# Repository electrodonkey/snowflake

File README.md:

# snowflake

RF controlled Christmas decoration

## architecture

- MCU: TI MSPM0L1306
- LED DRIVER: TI LP5569
- SUB-GHz: ST S2-LP
- POWER: CR2032

## hardware

[schematic pdf](hardware/output/snowflake.pdf)

## licence

Copyright 2023 Dan Chirciu (electrodonkey)

Permission is hereby granted, free of charge, to any person obtaining a copy of this software and associated documentation files (the “Software”), to deal in the Software without restriction, including without limitation the rights to use, copy, modify, merge, publish, distribute, sublicense, and/or sell copies of the Software, and to permit persons to whom the Software is furnished to do so, subject to the following conditions:

The above copyright notice and this permission notice shall be included in all copies or substantial portions of the Software.

THE SOFTWARE IS PROVIDED “AS IS”, WITHOUT WARRANTY OF ANY KIND, EXPRESS OR IMPLIED, INCLUDING BUT NOT LIMITED TO THE WARRANTIES OF MERCHANTABILITY, FITNESS FOR A PARTICULAR PURPOSE AND NONINFRINGEMENT. IN NO EVENT SHALL THE AUTHORS OR COPYRIGHT HOLDERS BE LIABLE FOR ANY CLAIM, DAMAGES OR OTHER LIABILITY, WHETHER IN AN ACTION OF CONTRACT, TORT OR OTHERWISE, ARISING FROM, OUT OF OR IN CONNECTION WITH THE SOFTWARE OR THE USE OR OTHER DEALINGS IN THE SOFTWARE.

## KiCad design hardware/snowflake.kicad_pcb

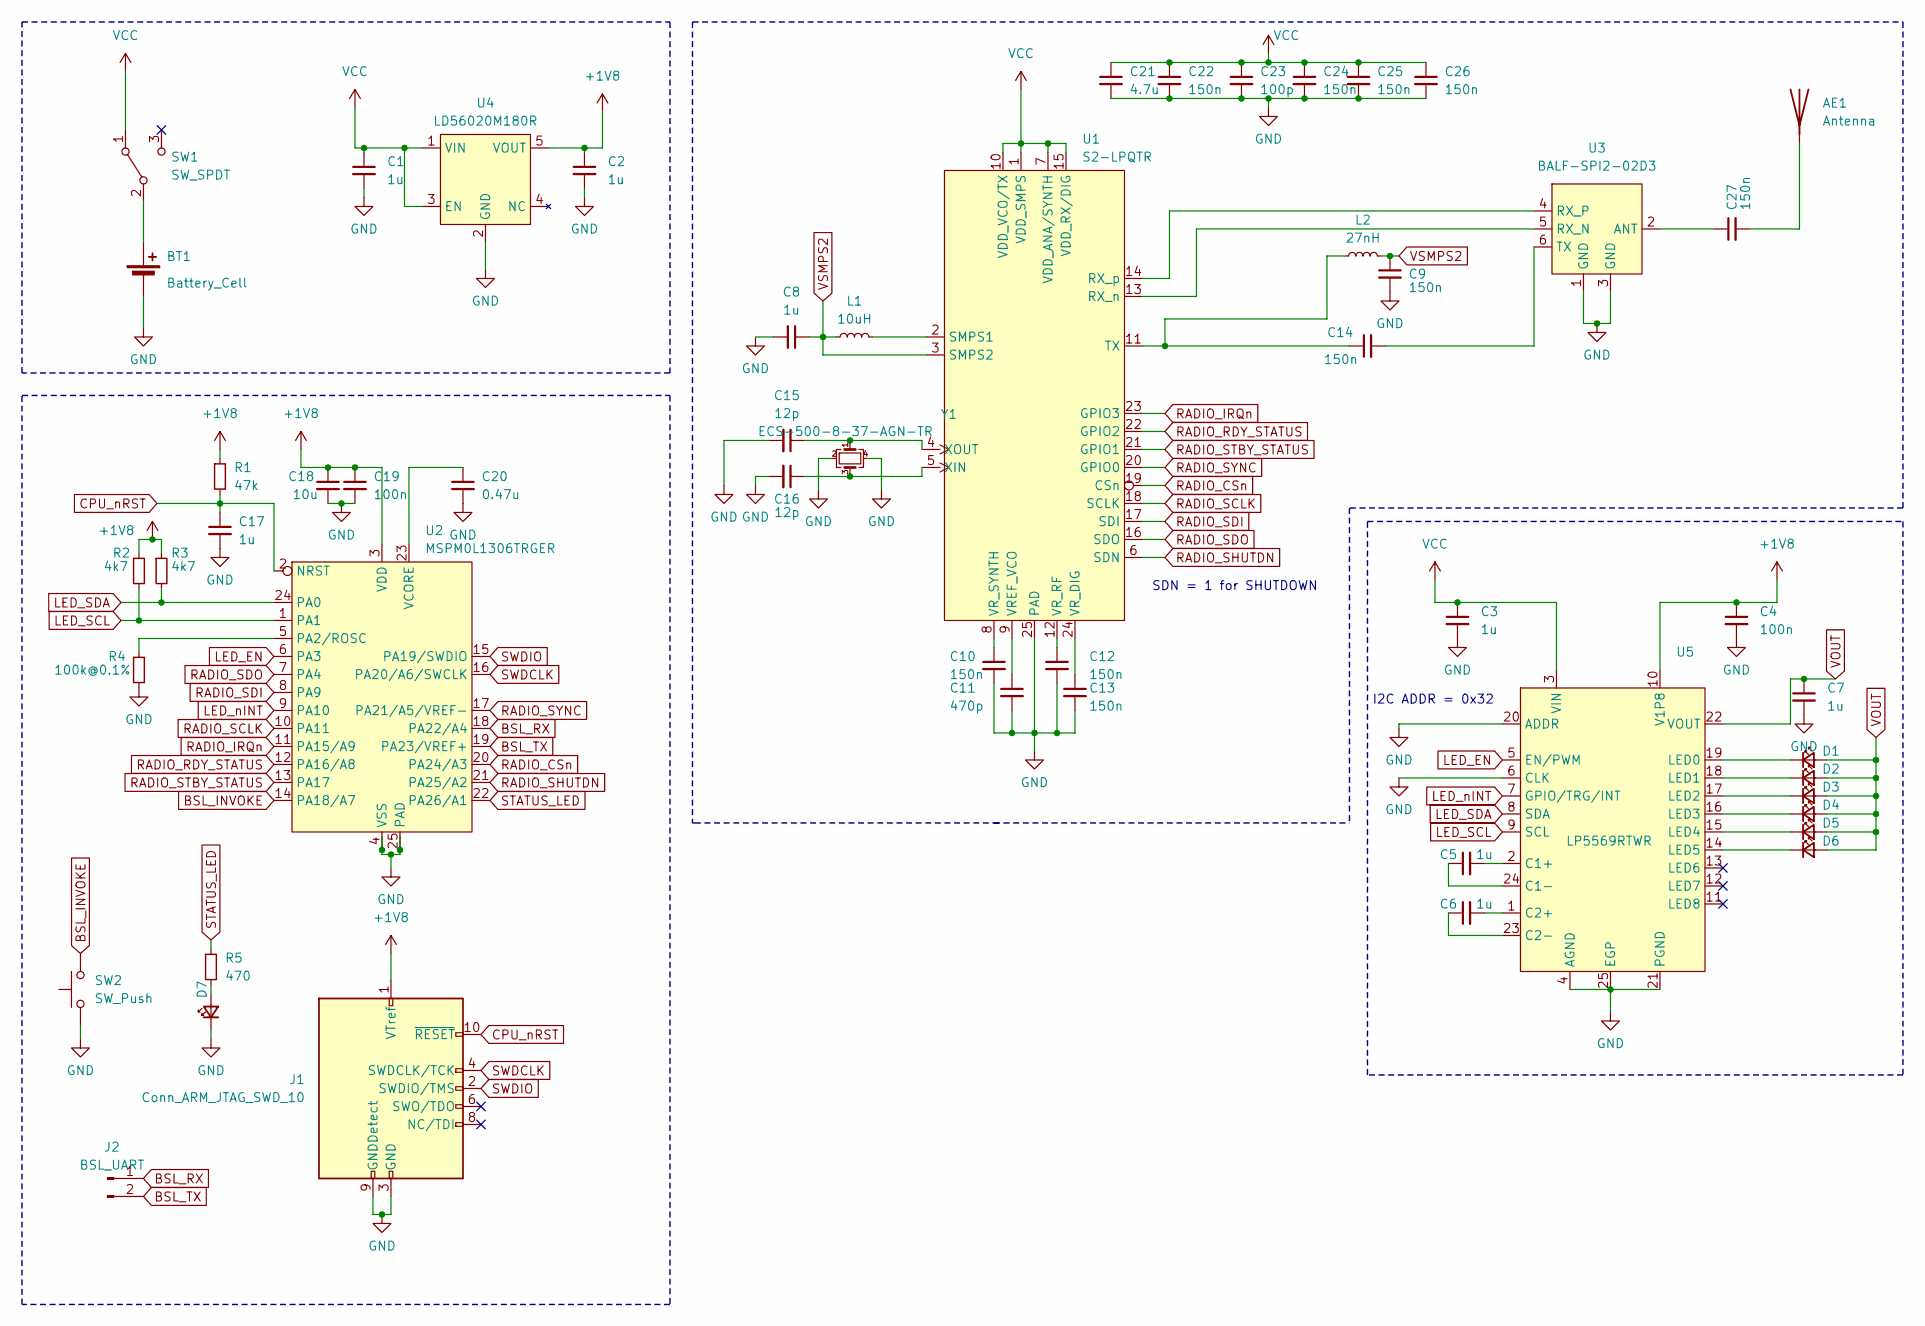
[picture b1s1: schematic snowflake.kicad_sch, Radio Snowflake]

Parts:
AE1: Antenna; ANT-418-HETH
BT1: Battery_Cell; BatteryHolder_Keystone_3034_1x20mm
C1, C2, C3, C5, C6, C7, C8, C17: 1u; C_0603_1608Metric_Pad1.08x0.95mm_HandSolder
C4, C19: 100n; C_0603_1608Metric_Pad1.08x0.95mm_HandSolder
C9, C10, C12, C13, C14, C22, C24, C25, C26, C27: 150n; C_0603_1608Metric_Pad1.08x0.95mm_HandSolder
C11: 470p; C_0603_1608Metric_Pad1.08x0.95mm_HandSolder
C15, C16: 12p; C_0603_1608Metric_Pad1.08x0.95mm_HandSolder
C18: 10u; C_0603_1608Metric_Pad1.08x0.95mm_HandSolder
C20: 0.47u; C_0603_1608Metric_Pad1.08x0.95mm_HandSolder
C21: 4.7u; C_0603_1608Metric_Pad1.08x0.95mm_HandSolder
C23: 100p; C_0603_1608Metric_Pad1.08x0.95mm_HandSolder
D1, D2, D3, D4, D5, D6, D7: LED; LED_1206_3216Metric_Pad1.42x1.75mm_HandSolder
J1: Conn_ARM_JTAG_SWD_10; PinHeader_2x05_P1.27mm_Vertical
J2: BSL_UART; PinHeader_1x02_P1.27mm_Vertical
L1: 10uH; L_0603_1608Metric_Pad1.05x0.95mm_HandSolder
L2: 27nH; L_0603_1608Metric_Pad1.05x0.95mm_HandSolder
R1: 47k; R_0603_1608Metric_Pad0.98x0.95mm_HandSolder
R2, R3: 4k7; R_0603_1608Metric_Pad0.98x0.95mm_HandSolder
R4: 100k@0.1%; R_0603_1608Metric_Pad0.98x0.95mm_HandSolder
R5: 470; R_0603_1608Metric_Pad0.98x0.95mm_HandSolder
SW1: SW_SPDT; SW_SPDT_PCM12
SW2: SW_Push; SW_SPST_Omron_B3FS-100xP
U1: S2-LPQTR; QFN-24-1EP_4x4mm_P0.5mm_EP2.7x2.7mm
U2: MSPM0L1306TRGER; Texas_RGE0024C_EP2.1x2.1mm
U3: BALF-SPI2-02D3; balf-spi2-01d3
U4: LD56020M180R; SOT-23-5_HandSoldering
U5: LP5569RTWR; WQFN-24-1EP_4x4mm_P0.5mm_EP2.6x2.6mm
Y1: ECS-500-8-37-AGN-TR; Crystal_SMD_2016-4Pin_2.0x1.6mm

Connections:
+1V8: C2.1, C4.1, C18.1, C19.1, J1.1 (VTref), R1.1, R2.1, R3.1, U2.3 (VDD), U4.5 (VOUT), U5.10 (V1P8)
BSL_INVOKE: SW2.2, U2.14 (PA18/A7)
BSL_RX: J2.1, U2.18 (PA22/A4)
BSL_TX: J2.2, U2.19 (PA23/VREF+)
CPU_nRST: C17.1, J1.10 (~RESET), R1.2, U2.2 (NRST)
GND: BT1.2 (-), C1.2, C2.2, C3.2, C4.2, C7.2, C8.2, C9.2, C10.2, C11.2, C12.2, C13.2, C15.2, C16.2, C17.2, C18.2, C19.2, C20.2, C21.2, C22.2, C23.2, C24.2, C25.2, C26.2, D7.1 (K), J1.3 (GND), J1.5 (GND), J1.9 (GNDDetect), R4.2, SW2.1, U1.25 (PAD), U2.4 (VSS), U2.25 (PAD), U3.1 (GND), U3.3 (GND), U4.2 (GND), U5.4 (AGND), U5.6 (CLK), U5.20 (ADDR), U5.21 (PGND), U5.25 (EGP), Y1.2, Y1.4
LED_EN: U2.6 (PA3), U5.5 (EN/PWM)
LED_SCL: R2.2, U2.1 (PA1), U5.9 (SCL)
LED_SDA: R3.2, U2.24 (PA0), U5.8 (SDA)
LED_nINT: U2.9 (PA10), U5.7 (GPIO/TRG/INT)
unnamed: AE1.1 (A), C27.2
unnamed: BT1.1 (+), SW1.2 (B)
unnamed: D1.1 (K), U5.19 (LED0)
unnamed: D2.1 (K), U5.18 (LED1)
unnamed: D3.1 (K), U5.17 (LED2)
unnamed: D4.1 (K), U5.16 (LED3)
unnamed: D5.1 (K), U5.15 (LED4)
unnamed: D6.1 (K), U5.14 (LED5)
unnamed: D7.2 (A), R5.2
unnamed: U1.13 (RX_n), U3.5 (RX_N)
unnamed: U1.14 (RX_p), U3.4 (RX_P)
unnamed: L1.2, U1.2 (SMPS1)
unnamed: C14.1, L2.1, U1.11 (TX)
unnamed: C11.1, U1.9 (VREF_VCO)
unnamed: C13.1, U1.24 (VR_DIG)
unnamed: C12.1, U1.12 (VR_RF)
unnamed: C10.1, U1.8 (VR_SYNTH)
unnamed: C16.1, U1.5 (XIN), Y1.3
unnamed: C15.1, U1.4 (XOUT), Y1.1
unnamed: R4.1, U2.5 (PA2/ROSC)
unnamed: C20.1, U2.23 (VCORE)
unnamed: C27.1, U3.2 (ANT)
unnamed: C14.2, U3.6 (TX)
unnamed: C5.2, U5.2 (C1+)
unnamed: C5.1, U5.24 (C1-)
unnamed: C6.2, U5.1 (C2+)
unnamed: C6.1, U5.23 (C2-)
RADIO_CSn: U1.19 (CSn), U2.20 (PA24/A3)
RADIO_IRQn: U1.23 (GPIO3), U2.11 (PA15/A9)
RADIO_RDY_STATUS: U1.22 (GPIO2), U2.12 (PA16/A8)
RADIO_SCLK: U1.18 (SCLK), U2.10 (PA11)
RADIO_SDI: U1.17 (SDI), U2.8 (PA9)
RADIO_SDO: U1.16 (SDO), U2.7 (PA4)
RADIO_SHUTDN: U1.6 (SDN), U2.21 (PA25/A2)
RADIO_STBY_STATUS: U1.21 (GPIO1), U2.13 (PA17)
RADIO_SYNC: U1.20 (GPIO0), U2.17 (PA21/A5/VREF-)
STATUS_LED: R5.1, U2.22 (PA26/A1)
SWDCLK: J1.4 (SWDCLK/TCK), U2.16 (PA20/A6/SWCLK)
SWDIO: J1.2 (SWDIO/TMS), U2.15 (PA19/SWDIO)
VCC: C1.1, C3.1, C21.1, C22.1, C23.1, C24.1, C25.1, C26.1, SW1.1 (A), U1.1 (VDD_SMPS), U1.7 (VDD_ANA/SYNTH), U1.10 (VDD_VCO/TX), U1.15 (VDD_RX/DIG), U4.1 (VIN), U4.3 (EN), U5.3 (VIN)
VOUT: C7.1, D1.2 (A), D2.2 (A), D3.2 (A), D4.2 (A), D5.2 (A), D6.2 (A), U5.22 (VOUT)
VSMPS2: C8.1, C9.1, L1.1, L2.2, U1.3 (SMPS2)

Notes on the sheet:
I2C ADDR = 0x32
SDN = 1 for SHUTDOWN

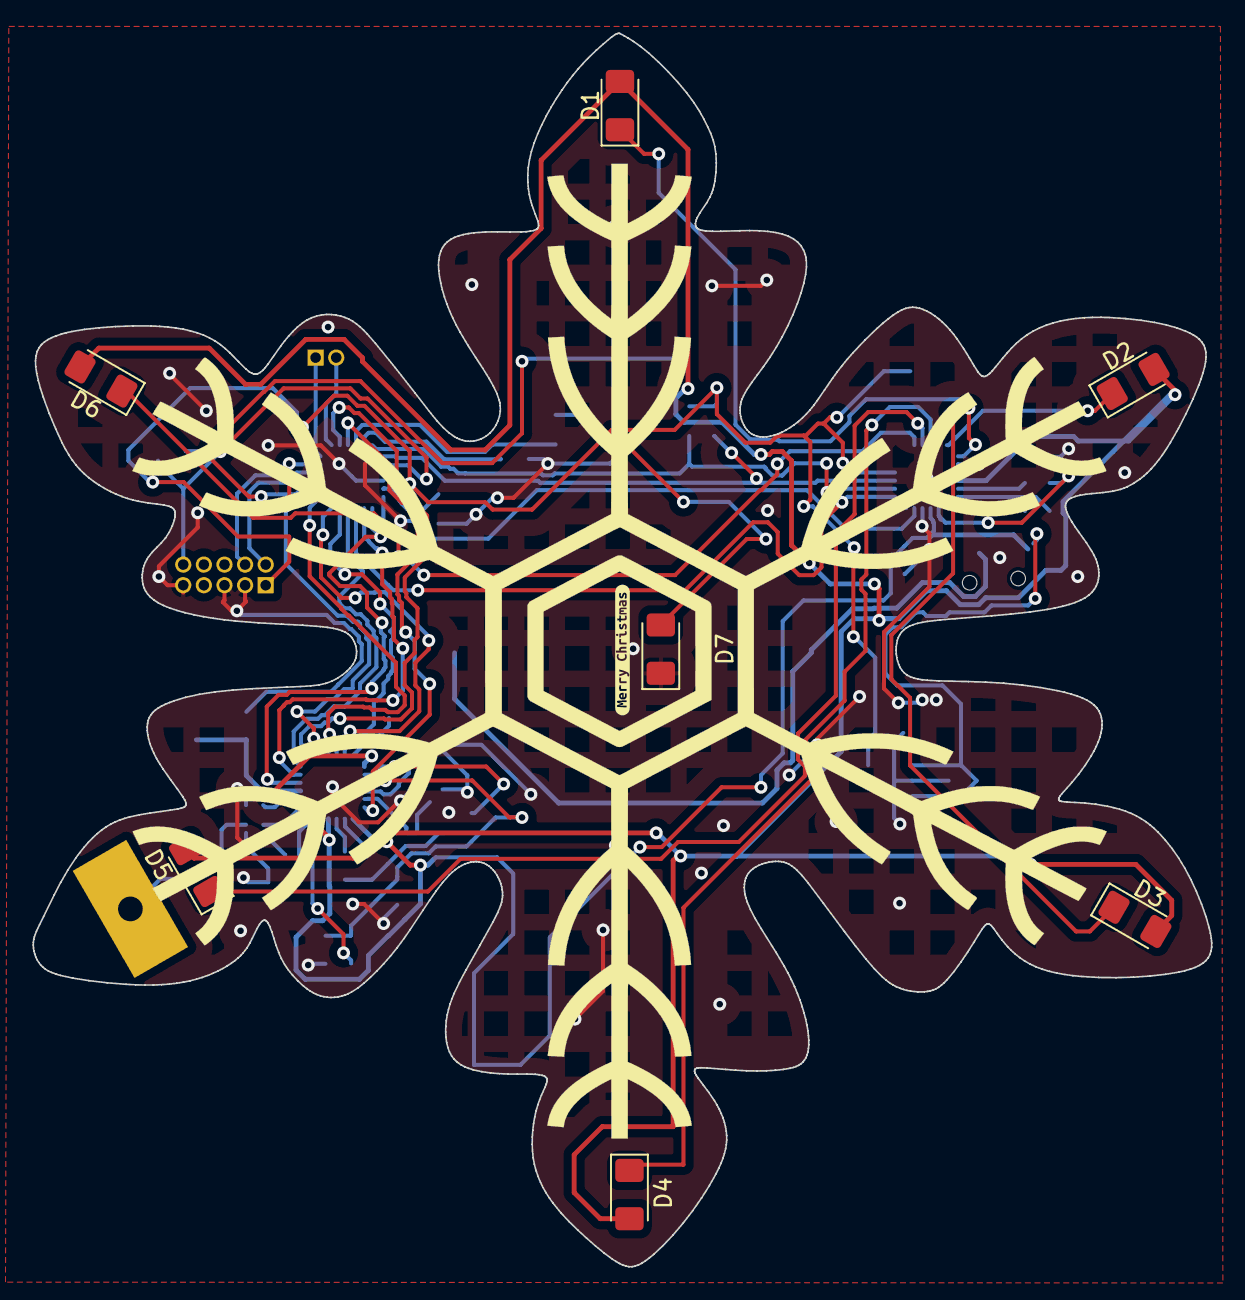
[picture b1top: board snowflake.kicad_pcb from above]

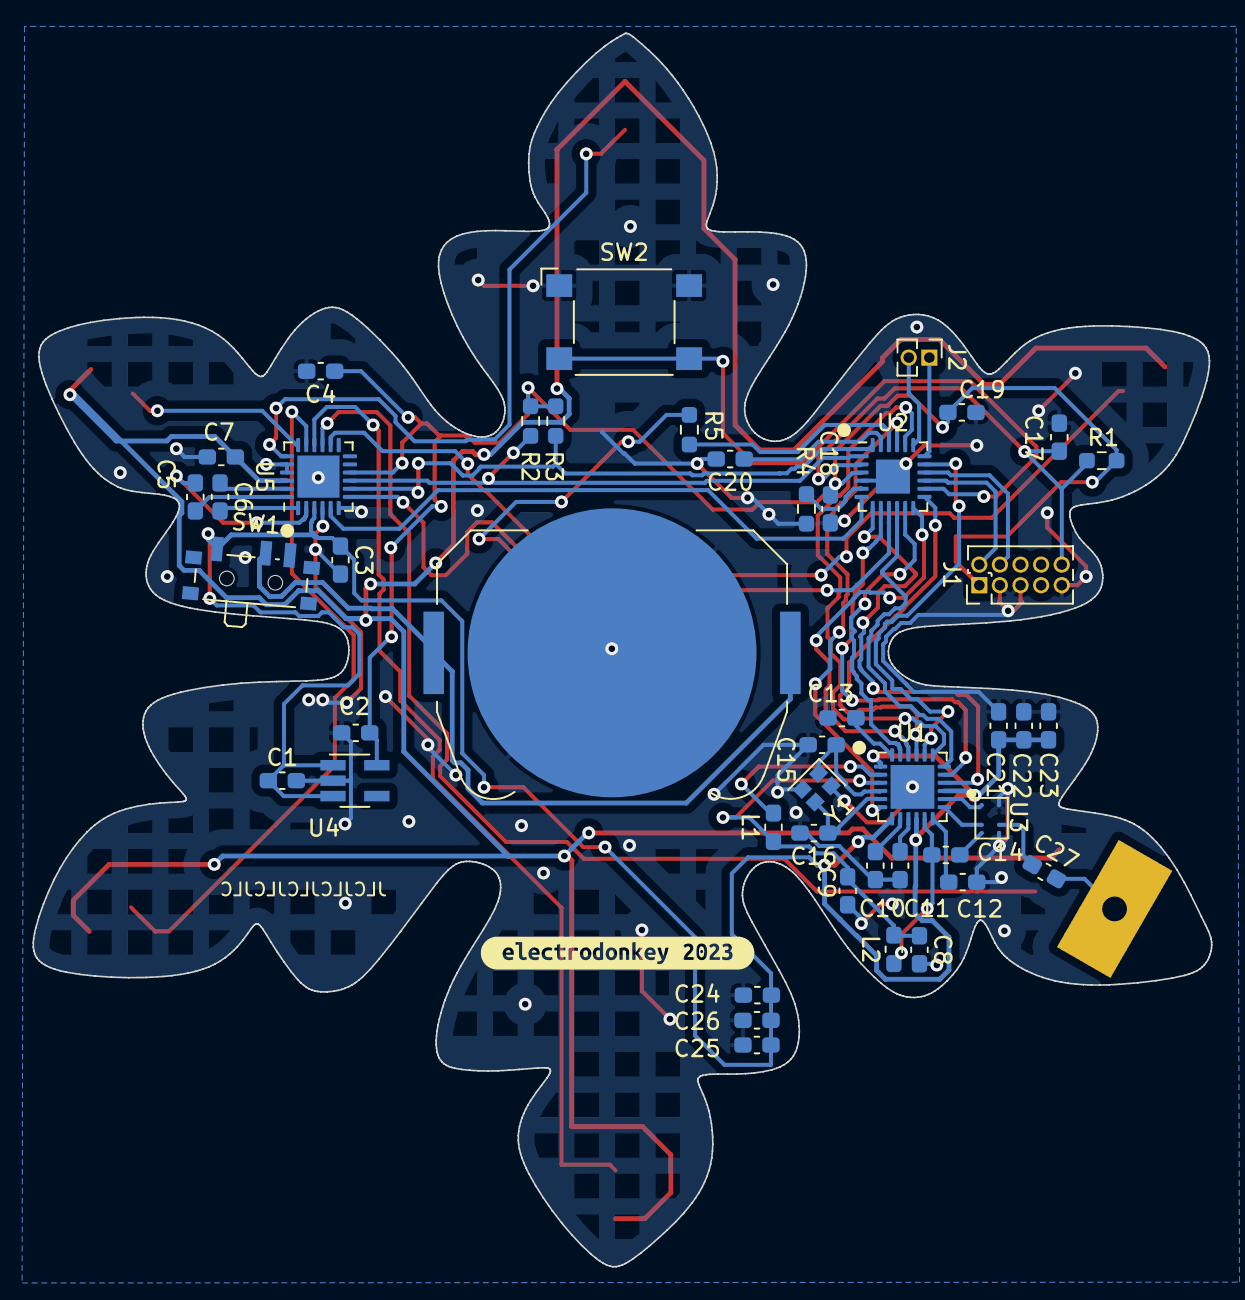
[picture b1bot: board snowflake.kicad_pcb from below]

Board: 2 copper layers, 72.6 x 76.0 mm, 56 parts (47 on the bottom side), 52 nets.

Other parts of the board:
Ref**: Val**; snowflake_man
kibuzzard-65665C77: G***; kibuzzard-65665C77
kibuzzard-65665DDA: G***; kibuzzard-65665DDA

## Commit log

2023-12-28 Add .gitignore
2023-12-28 Add snowflake project to github

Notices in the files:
hardware/snowflake.kicad_sch:
Solderpad Hardware License
